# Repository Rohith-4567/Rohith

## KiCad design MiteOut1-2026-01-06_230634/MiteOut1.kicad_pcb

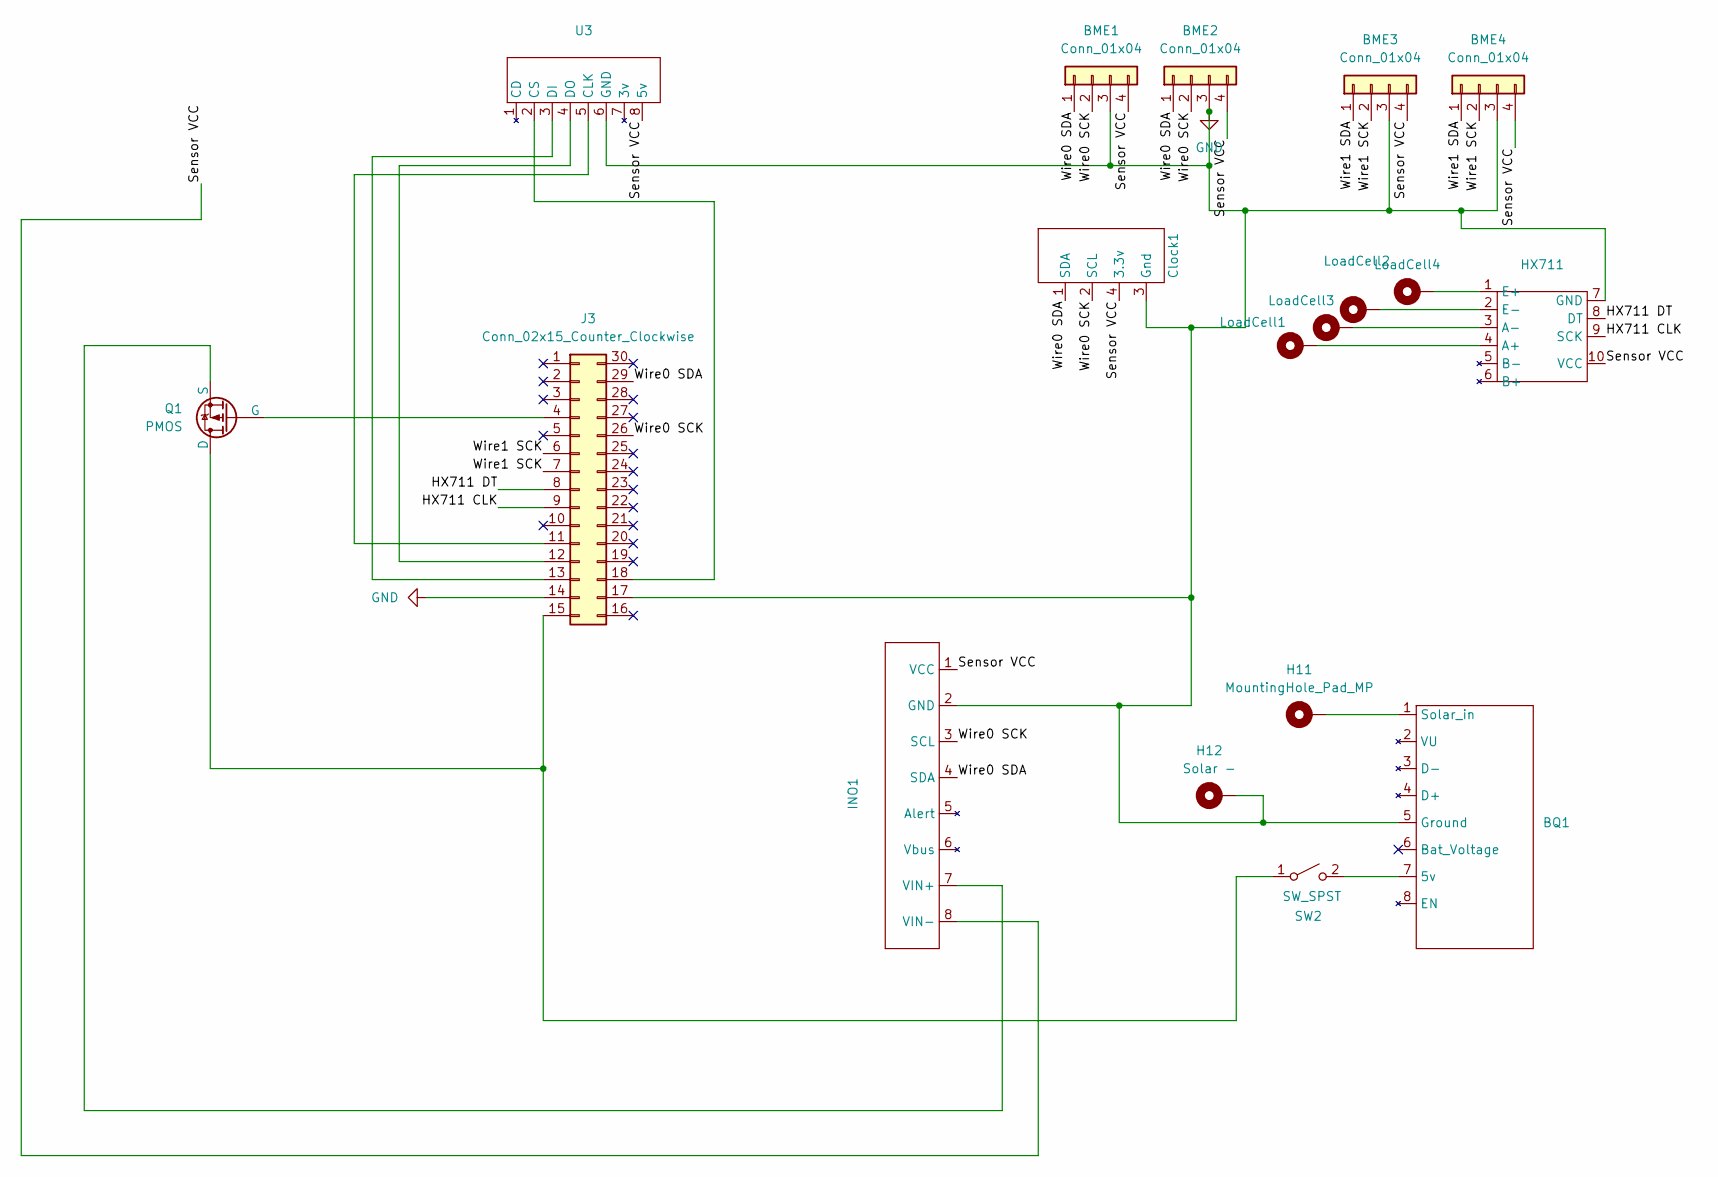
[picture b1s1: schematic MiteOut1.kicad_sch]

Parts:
BME1, BME2, BME3, BME4: Conn_01x04; 4Wire
BQ1: Charger
Clock1: Clock; 4Wire
H1: LoadCell3; throughole
H2: LoadCell1; throughole
H3: LoadCell4; throughole
H4: LoadCell2; throughole
H11: MountingHole_Pad_MP; throughole
H12: Solar -; throughole
HX711: hx711
INO1: INA
J3: Conn_02x15_Counter_Clockwise; ESP
Q1: PMOS; Mosfet
SW2: SW_SPST; SW_DIP_SPSTx01_Slide_6.7x4.1mm_W7.62mm_P2.54mm_LowProfile
U3: SDCard

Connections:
/HX711 CLK: HX711.9 (SCK), J3.9
/HX711 DT: HX711.8 (DT), J3.8
/Sensor VCC: BME1.4, BME2.4, BME3.4, BME4.4, Clock1.4 (3.3v), HX711.10 (VCC), INO1.1 (VCC), INO1.8 (VIN-), U3.8 (5v)
/Wire0 SCK: BME1.2, BME2.2, Clock1.2 (SCL), INO1.3 (SCL), J3.26
/Wire0 SDA: BME1.1, BME2.1, Clock1.1 (SDA), INO1.4 (SDA), J3.29
/Wire1 SCK: BME3.2, BME4.2, J3.6, J3.7
/Wire1 SDA: BME3.1, BME4.1
unnamed: BQ1.7 (5v), SW2.2 (B)
unnamed: BQ1.1 (Solar_in), H11.MP
unnamed: H2.MP, HX711.4 (A+)
unnamed: H1.MP, HX711.3 (A-)
unnamed 11: H3.MP, HX711.1 (E+); also elsewhere on the board
unnamed: H4.MP, HX711.2 (E-)
unnamed: INO1.7 (VIN+), Q1.1 (S)
unnamed: J3.4, Q1.3 (G)
unnamed: J3.11, U3.5 (CLK)
unnamed: J3.12, U3.4 (DO)
unnamed: J3.13, U3.3 (DI)
unnamed: J3.15, Q1.2 (D), SW2.1 (A)
unnamed: J3.18, U3.2 (CS)

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
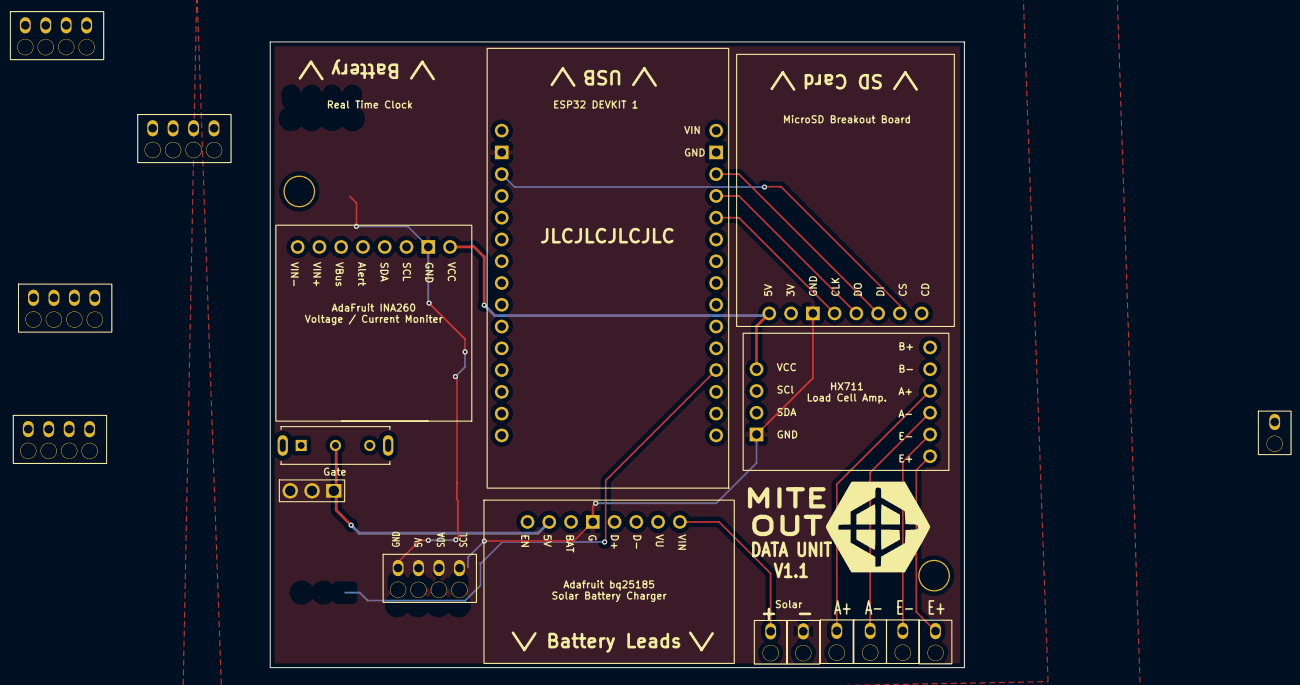
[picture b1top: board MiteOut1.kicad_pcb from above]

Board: 2 copper layers, 81.0 x 73.0 mm, 19 parts (0 on the bottom side), 21 nets.

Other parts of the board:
H3#2: LoadCell4; throughole

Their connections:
unnamed 11: H3#2.MP; also elsewhere on the board

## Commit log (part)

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2026-05-27 initial
2026-05-27 move
2026-05-27 move back
2026-05-27 added new sch
2026-05-27 finished batt board
2026-05-27 quick fix
2026-05-29 added SD Card
2026-05-29 SD Card edits
2026-05-29 Finished MicroSD
2026-05-30 Finished ADC + ESP needing edits
2026-05-31 finished RTC
2026-05-31 some changes ig
2026-06-01 Full Schematic Draft 1
2026-06-01 some error fixes
2026-06-03 Fully checked schematic
